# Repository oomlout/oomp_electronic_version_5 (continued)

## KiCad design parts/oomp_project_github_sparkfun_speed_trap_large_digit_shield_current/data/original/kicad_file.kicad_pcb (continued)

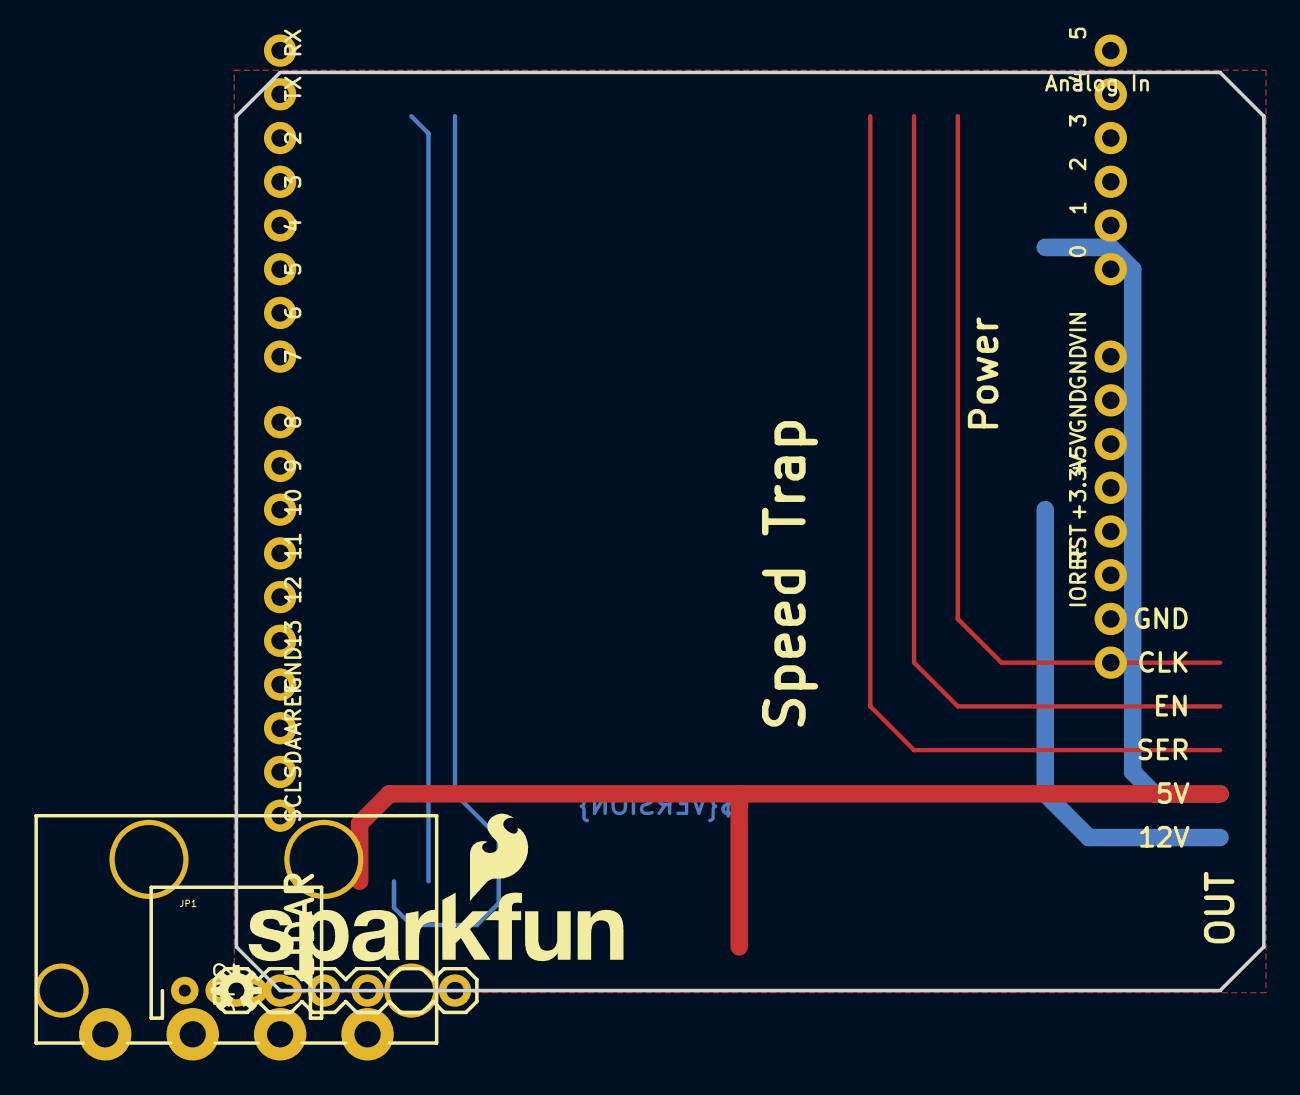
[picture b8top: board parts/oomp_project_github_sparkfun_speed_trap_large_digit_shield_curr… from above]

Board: 2 copper layers, 59.7 x 53.3 mm, 7 parts (0 on the bottom side), 8 nets.
